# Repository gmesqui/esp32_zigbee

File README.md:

# ESP32-C5 / ESP32-C6 Zigbee Coordinator

Coordinador Zigbee completo para `ESP32-C5-KITC-A V1.2` y `ESP32-C6 Super Mini` con `ESP-IDF` y `ESP Zigbee SDK`.

Todo dispositivo con microcontrolador del proyecto debe admitir actualizaciones por su red de comunicaciones. La conexión física al ordenador queda como último recurso. El estado de los firmwares existentes y los criterios de aceptación se recogen en el [plan de actualización por red](PLAN.md).

## Hardware soportado

| Placa | Target ESP-IDF | Radio | Flash | LED RGB | Boton permit-join |
|-------|----------------|-------|-------|---------|-------------------|
| `ESP32-C5-KITC-A V1.2` | `esp32c5` | IEEE 802.15.4 nativa 2.4 GHz | 4 MiB | WS2812 GPIO 27 | GPIO 28 |
| `ESP32-C6 Super Mini` | `esp32c6` | IEEE 802.15.4 nativa 2.4 GHz | 4 MiB | WS2812 GPIO 8 | GPIO 9 |

- Ethernet: W5500 por SPI (`SPI2_HOST`)
- Consola: UART0 115200 baud en C5; USB Serial/JTAG nativo por USB-C en C6 Super Mini.
- La seleccion de pines se hace en `main/board_config.h` usando `CONFIG_IDF_TARGET`.

---

## Transporte WebSocket

El transporte operativo para clientes externos es WebSocket sobre ESP-IDF:

- Nombre mDNS del coordinador: `esp32-zigbee.local`
- Panel web: `http://esp32-zigbee.local:8080/`
- URL: `ws://esp32-zigbee.local:8080/ws`
- Modulo servidor: `ws_transport.c/h`
- Protocolo y parsing: `ws_protocol.c/h`
- Adaptacion del modelo interno: `ws_model.c/h`
- Sesion activa: `ws_client_session.c/h`
- Puente de productores Zigbee/modelo: `client_events.c/h`
- Self-test por UART: tecla `w`

Al conectarse un cliente, el ESP32 inicia el stream autonomo sin esperar un
mensaje entrante: envia `hello_ack`, inventario fragmentado, estado inicial y
despues queda en modo stream para eventos futuros.

---

## Arquitectura

```
app_main()
  ├─ nvs_flash_init()
  ├─ dm_init()              ← tabla RAM de dispositivos
  ├─ nvs_cache_load()       ← restaura registros desde NVS
  ├─ zcl_handler_init()     ← cache de atributos
  ├─ di_init()              ← maquina de estados de entrevista
  ├─ led_driver_init()      ← tarea LED @ 50 Hz
  ├─ button_handler_init()  ← ISR boton BOOT
  ├─ serial_cmd_init()      ← tarea UART0
  └─ zigbee_core_init()     ← tarea Zigbee + main loop (nunca retorna)
```

### Tareas FreeRTOS

| Tarea | Prioridad | Proposito |
|-------|-----------|-----------|
| `zigbee_main` | 5 | Loop principal del stack Zigbee |
| `btn_task` | 3 | Procesador de eventos de boton |
| `led_task` | 2 | Animacion LED @ 50 Hz |
| `serial_cmd_task` | 1 | Listener consola activa (`UART0` en C5, `USB Serial/JTAG` en C6) |

### Ficheros fuente

| Fichero | Responsabilidad |
|---------|----------------|
| `main.c` | Punto de entrada, secuencia de inicializacion |
| `board_config.h` | Seleccion de placa, pines de LED/boton/Ethernet y nombre de hardware por target ESP-IDF |
| `zigbee_core.c/h` | Init coordinador, manejador de senales BDB/ZDO, manejador de acciones ZCL, alarmas de mantenimiento |
| `device_manager.c/h` | Tabla RAM thread-safe (max 32 dispositivos), ciclo de vida, lookups por IEEE/NWK |
| `device_interview.c/h` | Maquina de estados de entrevista (7 pasos), cola FIFO, callbacks ZDO, resolucion IEEE |
| `zcl_handler.c/h` | Decodificacion de Report Attributes y Read Attribute Responses, cache con deteccion de cambios |
| `report_config.c/h` | Envio de Configure Reporting tras entrevista (13 clusters), respuesta IAS enrollment |
| `nvs_cache.c/h` | Serializacion/deserializacion binaria de dispositivos en NVS, escrituras lazy por bandera dirty |
| `serial_cmd.c/h` | Comandos interactivos por consola activa (teclas 1–5, g, w, n, j, r, e, ?) |
| `led_driver.c/h` | Control WS2812: onda seno verde-azul base, overlay rojo permit-join, overlay blanco actividad |
| `button_handler.c/h` | ISR con antirebote 200 ms, toggle permit-join 180 s |
| `utils.c/h` | Uptime ms/s, IEEE→string, nombres de cluster/device-type, macro `ZB_LOG` con timestamp |

---

## Funcionalidades implementadas

### Coordinador Zigbee

- Perfil Home Automation (0x0104), dispositivo Home Gateway (0x0050)
- Radio nativa, sin modo host
- Max 20 hijos (routers + end devices)
- Endpoint 1 con clusters Basic e Identify
- Mascara de canales: todos los canales 2.4 GHz
- Persistencia de red en NVS (namespace Zigbee stack): canal, PAN ID, ext PAN ID, clave de red

### Tabla de dispositivos en RAM

- 32 slots, protegida con mutex
- Estado por dispositivo: `NEW` → `INTERVIEWING` → `INTERVIEWED` → `CONFIGURED` → `FAILED`
- Campos por dispositivo:
  - `ieee`, `nwk_addr`, `friendly_name`
  - `online`, `is_sleepy`
  - `manufacturer`, `model`, `power_source`
  - `node_desc_flags`, `mac_capability_flags`, `manufacturer_code`, `power_desc_flags`
  - Hasta 8 endpoints, cada uno con `profile_id`, `device_id`, `clusters_in[]`, `clusters_out[]`
  - `last_seen_ms`, `lqi`, `rssi`
  - `reporting_configured`
  - Lecturas: `temperature_c`, `humidity_pct`, `on_off`, `occupancy`, `illuminance_raw`, `illuminance_lux`, `pressure_kpa`, `ias_zone_status`, `battery_mv`, `battery_pct`, `level`, `power_watts`
  - Contadores: `report_attr_ok`, `report_attr_unchanged`, `read_rsp_ok`, `read_rsp_fail`, `interview_attempts`

### Entrevista automatica (7 pasos)

1. Node Descriptor Request (ZDO)
2. Power Descriptor Request (ZDO)
3. Active Endpoints Request (ZDO)
4. Simple Descriptor Request por endpoint (ZDO)
5. Read Basic Cluster (0x0000, attrs: fabricante, modelo, fuente de alimentacion)
6. Read Power Config (0x0001, attrs: tension y porcentaje de bateria)
7. Configure Reporting (13 clusters estandar)

- Reintentos: 3 con backoff; marca FAILED si se agotan
- Cola FIFO de 8 posiciones para joins simultaneos
- Resolucion asıncrona de IEEE Address si se desconoce la direccion corta

### Clusters soportados para reporte / lectura

| Cluster | Nombre | Atributos relevantes |
|---------|--------|----------------------|
| 0x0001 | POWER_CFG | Tension bateria (0x0020), porcentaje (0x0021) |
| 0x0006 | ON_OFF | Estado encendido (0x0000) |
| 0x0008 | LEVEL | Nivel (0x0000, 0–254) |
| 0x0300 | COLOR_CTRL | Hue, Saturation, Color Temperature |
| 0x0400 | ILLUMINANCE | Iluminancia raw + conversion log a lux |
| 0x0402 | TEMPERATURE | Temperatura int16 ÷ 100 → °C |
| 0x0403 | PRESSURE | Presion int16 ÷ 10 → kPa |
| 0x0405 | HUMIDITY | Humedad uint16 ÷ 100 → % |
| 0x0406 | OCCUPANCY | Bitmap presencia |
| 0x0500 | IAS_ZONE | Estado zona alarma + enrollment |
| 0x0B04 | ELEC_MEAS | Potencia activa (0x050B) |

### Configure Reporting enviado tras entrevista

| Cluster | Atributo | Tipo | Min (s) | Max (s) | Threshold |
|---------|----------|------|---------|---------|-----------|
| 0x0006 | 0x0000 | bool | 0 | 3600 | — |
| 0x0008 | 0x0000 | uint8 | 1 | 3600 | 1 |
| 0x0300 | 0x0000, 0x0001 | uint8 | 1 | 3600 | 1 |
| 0x0300 | 0x0007 | uint16 | 1 | 3600 | 10 |
| 0x0402 | 0x0000 | int16 | 10 | 3600 | 10 |
| 0x0405 | 0x0000 | uint16 | 10 | 3600 | 50 |
| 0x0403 | 0x0000 | int16 | 10 | 3600 | 10 |
| 0x0400 | 0x0000 | uint16 | 10 | 3600 | 500 |
| 0x0406 | 0x0000 | bitmap8 | 0 | 3600 | — |
| 0x0001 | 0x0021 | uint8 | 3600 | 43200 | 2 |
| 0x0500 | 0x0002 | bitmap16 | 0 | 3600 | — |
| 0x0B04 | 0x050B | int16 | 5 | 3600 | 10 |

### Deteccion de presencia (offline)

- **Siempre encendido**: lectura de confirmacion al llegar a `max_interval + presence_probe_grace_s`; offline al llegar a `max_interval + presence_offline_grace_s` si no hubo respuesta.
- **Sleepy (bateria)**: sin sondeo activo; offline al llegar a `max_interval + presence_offline_grace_s`.
- Verificacion cada 10 s via alarma de mantenimiento
- Para dispositivos siempre encendidos, `presence_probe_grace_s` es el margen bajo que dispara una lectura ZCL de confirmacion; `presence_offline_grace_s` es el margen alto que certifica offline si no hubo respuesta ni otro trafico.

### Persistencia NVS de dispositivos

- Namespace: `zb_cache`
- Claves: `dt3_head` (version + count), `dt3_d00`–`dt3_d31` (blobs por dispositivo)
- Version de esquema: **3** (los blobs de versiones anteriores se rechazan)
- Escritura lazy: solo los registros con bandera `dirty` se escriben; se limpia tras commit
- Periodicidad: cada 10 s via alarma de mantenimiento (solo si hay cambios)
- Al arrancar: los dispositivos restaurados vuelven con estado INTERVIEWED, `online=false`
- `last_seen` y cambios de RSSI/LQI NO disparan escritura NVS

> Si ves `ESP_ERR_NVS_NOT_ENOUGH_SPACE` al guardar `dt3_d31`, no reduzcas la particion `nvs` (actualmente 128 KiB).

### LED WS2812

| Estado | Patron |
|--------|--------|
| Normal | Onda seno verde-azul, periodo 4 s |
| Permit-join abierto | Overlay rojo pulsante, periodo 1 s |
| Actividad ZCL | Flash blanco 100 ms con decay |

### Boton BOOT

- Pulsacion corta: abre permit-join 180 s (o cierra si ya estaba abierto)
- Antirebote hardware: 200 ms

### Patillaje Ethernet (W5500 por SPI)

| Senal | ESP32-C5 GPIO | ESP32-C6 GPIO | Notas |
|-------|---------------|---------------|-------|
| `MOSI` | 4 | 2 | SPI hacia el W5500 |
| `MISO` | 5 | 3 | SPI desde el W5500 |
| `SCLK` | 6 | 6 | Reloj SPI |
| `CS` | 23 | 7 | Chip select del W5500 |
| `INT` | 24 | 18 | Interrupcion del W5500 |
| `RST` | 25 | 14 | Reset del W5500 |

- Host SPI usado: `SPI2_HOST`
- Frecuencia SPI configurada: `20 MHz`

---

## Comandos serie

Canal interactivo segun target:

- `ESP32-C5`: `UART0` a `115200`
- `ESP32-C6`: `USB Serial/JTAG` nativo por USB-C

| Tecla | Accion |
|-------|--------|
| `1` | Emite JSON completo con tabla de dispositivos |
| `2` | Estadisticas de red (canal, PAN ID, ext PAN ID, IEEE coordinador, conteo online) |
| `3` | Lista de tareas FreeRTOS (nombre, estado, prioridad, stack) |
| `4` | Estadisticas de heap (libre actual, minimo historico) |
| `5` | Estado de la cola de entrevista |
| `n` | Asignar nombre amigable a un dispositivo (pide IEEE y nombre) |
| `j` | Toggle permit-join (abre 180 s o cierra) |
| `r` | Re-entrevistar dispositivo (pide IEEE, resetea estado a NEW) |
| `e` | Borrar cache NVS (pide confirmacion "YES") |
| `w` | Ejecutar self-test del protocolo WebSocket |
| `?` | Ayuda: imprime mapa de teclas |

---

## Formato de log

Cuando el reloj SNTP ya es valido, los logs usan fecha y hora local segun la
zona horaria configurada. Mientras el reloj no sea valido, usan timestamp
relativo al arranque:

```
[2026-04-26 20:35:12.123]
[T+%07.3f]  ->  [T+012.345]
```

Por cada mensaje ZCL/ZDO se emiten hasta 3 lineas:

1. `RAW` — bytes en hexadecimal y metadatos APS/NWK
2. `DECODE` — campos interpretados (profile, cluster, seq, etc.)
3. `IMPACT` — significado del mensaje y evento local desencadenado

---

## Salida JSON (tecla `1`)

```json
{
  "ts_s": 123.456,
  "device_count": 2,
  "devices": [
    {
      "ieee": "0x00124B00AABBCCDD",
      "friendly_name": "Sensor salon",
      "short": "0x1234",
      "online": true,
      "is_sleepy": false,
      "manufacturer": "Sonoff",
      "model": "SNZB-02",
      "power_source": "battery",
      "state": "configured",
      "last_seen_s": 120.123,
      "lqi": 189,
      "rssi": -56,
      "reporting_configured": true,
      "endpoints": [
        {
          "id": 1,
          "profile": "0x0104",
          "device_id": "TEMP_SENSOR",
          "in_clusters": ["0x0000", "0x0001", "0x0003", "0x0402", "0x0405"],
          "out_clusters": ["0x0019"]
        }
      ],
      "readings": {
        "temperature_c": 21.45,
        "humidity_pct": 58.12,
        "battery_mv": 3000,
        "battery_pct": 85
      },
      "stats": {
        "report_attr_ok": 42,
        "report_attr_unchanged": 18,
        "read_rsp_ok": 7,
        "read_rsp_fail": 1,
        "interview_attempts": 1
      }
    }
  ]
}
```

Solo se incluyen en `readings` las claves que tienen dato (no se emiten `null`).
Si la iluminancia raw es 0 (demasiado baja), no se incluye `illuminance_lux`.

Comportamiento ante informes repetidos: `last_seen_s` se actualiza siempre; `report_attr_ok` y los logs de valor solo se emiten si el dato **cambia** respecto al almacenado; `report_attr_unchanged` cuenta los que no alteraron el dato.

---

## Limites y constantes clave

| Constante | Valor | Notas |
|-----------|-------|-------|
| `MAX_DEVICES` | 32 | Slots en tabla RAM |
| `MAX_ENDPOINTS` | 8 | Por dispositivo |
| `MAX_CLUSTERS_PER_EP` | 32 | Entrada + salida combinados |
| `FRIENDLY_NAME_LEN` | 33 | 32 chars + NUL |
| `MAX_ATTR_CACHE` | 128 | Entradas cache de atributos |
| `MAX_PENDING_ATTRS` | 8 | Buffer para direcciones desconocidas |
| `IQUEUE_SIZE` | 8 | Cola FIFO de entrevista |
| `MAX_CHILDREN` | 20 | Routers + end devices |
| `MAINTENANCE_PERIOD_MS` | 10 000 | NVS flush + deteccion presencia |
| `OFFLINE_THRESHOLD_ALWAYS_ON_MS` | 7 260 000 | ~2 h |
| `OFFLINE_THRESHOLD_SLEEPY_MS` | 10 920 000 | ~3 h |
| `PERMIT_JOIN_SECS` | 180 | Ventana abierta por boton |
| `DEBOUNCE_MS` | 200 | Antirebote boton |
| `LED_STRIP_GPIO` | C5: 27, C6: 8 | GPIO WS2812 |
| `BOOT_BUTTON_GPIO` | C5: 28, C6: 9 | GPIO boton BOOT |
| `ETH_MOSI_GPIO` | C5: 4, C6: 2 | SPI MOSI hacia W5500 |
| `ETH_MISO_GPIO` | C5: 5, C6: 3 | SPI MISO desde W5500 |
| `ETH_SCLK_GPIO` | C5: 6, C6: 6 | SPI clock W5500 |
| `ETH_CS_GPIO` | C5: 23, C6: 7 | Chip select W5500 |
| `ETH_INT_GPIO` | C5: 24, C6: 18 | Interrupcion W5500 |
| `ETH_RST_GPIO` | C5: 25, C6: 14 | Reset W5500 |
| `ETH_SPI_CLOCK_HZ` | 20 000 000 | SPI Ethernet a 20 MHz |
| `NVS_CACHE_VERSION` | 3 | Version de esquema NVS |

---

## Particiones

```
nvs,        data, nvs,     0x9000,   0x20000    # 128 KiB — NVS (cache + stack Zigbee)
phy_init,   data, phy,     0x29000,  0x1000     #   4 KiB — calibracion PHY
zb_storage, data, fat,     0x2A000,  0x10000    #  64 KiB — almacenamiento persistente Zigbee
zb_fct,     data, fat,     0x3A000,  0x1000     #   4 KiB — factory data Zigbee
otadata,    data, ota,     0x3C000,  0x2000
ota_0,      app,  ota_0,   0x40000,  0x1E0000
ota_1,      app,  ota_1,   0x220000, 0x1E0000
```

> Si cambias los offsets de `zb_storage` / `zb_fct`, hay que flashear la tabla de particiones y puede ser necesario volver a formar la red.

---

## Activar entorno ESP-IDF

Para macOS, consulta [Entorno de desarrollo en macOS](docs/entorno-macos.md),
con las herramientas instaladas, la activación del entorno y los comandos para
compilar ambas placas y ejecutar las aplicaciones del proyecto.

En PowerShell:

```powershell
. "C:\Espressif\tools\Microsoft.v5.5.3.PowerShell_profile.ps1"
```

## Compilar

Para ESP32-C5:

```powershell
idf.py set-target esp32c5
idf.py build
```

Para ESP32-C6:

```powershell
idf.py set-target esp32c6
idf.py build
```

`sdkconfig.defaults` contiene la configuracion comun, y `sdkconfig.defaults.esp32c5` / `sdkconfig.defaults.esp32c6` contienen los ajustes especificos de cada target.

## Actualizar por Ethernet

El coordinador C5 y el C6 admiten imágenes de aplicación firmadas sobre Ethernet. Para la migración de una unidad ya emparejada, la actualización ordinaria y la comprobación de dispositivos, sigue la [guía OTA](docs/ota-ethernet.md).

## Flashear y monitorizar

```powershell
.\flash-monitor.ps1
```

Solo monitorizar:

```powershell
.\monitor.ps1
```

Flashear con argumentos adicionales:

```powershell
.\idf-with-com7.ps1 flash monitor
```

En ESP32-C6 Super Mini, usa el puerto COM del USB-C nativo de la placa; `sdkconfig.defaults.esp32c6` deja la consola en USB Serial/JTAG.

Salir del monitor: `Ctrl+]`

---

## Plugin Homebridge

El plugin de Homebridge vive en una carpeta separada del firmware:

- [homebridge-plugin/README.md](/c:/projects/esp32_zigbee3/homebridge-plugin/README.md)

Se apoya en el protocolo WebSocket documentado en:

- [docs/protocolo_websocket_esp32_homebridge_v2.docx](/c:/projects/esp32_zigbee3/docs/protocolo_websocket_esp32_homebridge_v2.docx)

Objetivo del paquete:

- conectar Homebridge como cliente WebSocket al ESP32
- descubrir accesorios desde `inventory_chunk`
- mantener estado y reachability desde `state_chunk` y `event`
- traducir comandos HomeKit hacia `cmd`

El plugin se ha separado a nivel de repo para no mezclar dependencias Node/Homebridge
con el firmware ESP-IDF.

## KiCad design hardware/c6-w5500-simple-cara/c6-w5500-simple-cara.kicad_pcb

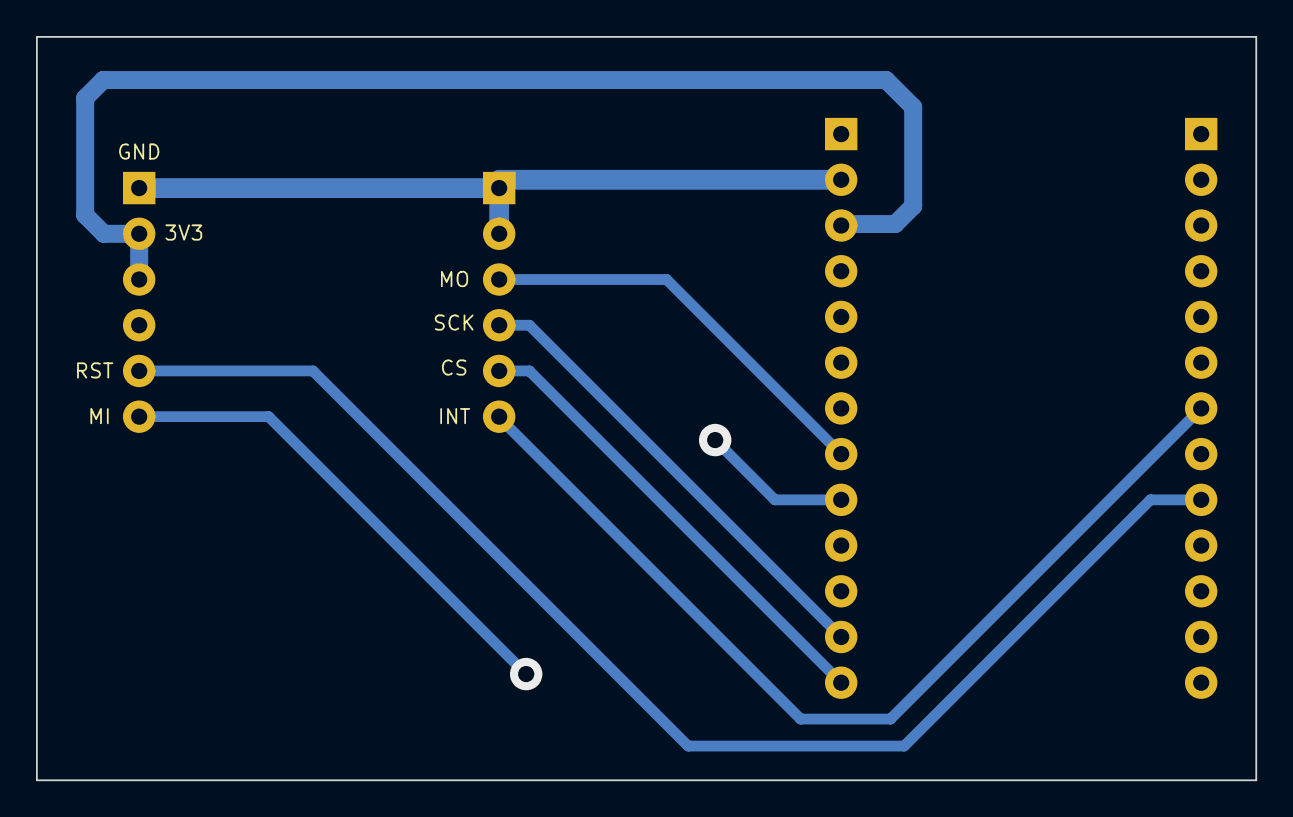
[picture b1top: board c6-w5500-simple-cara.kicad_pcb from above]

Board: 2 copper layers, 67.7 x 41.3 mm, 4 parts (0 on the bottom side), 8 nets.

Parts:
J1: W5500_LEFT; PinHeader_1x06_P2.54mm_Vertical
J2: W5500_RIGHT; PinHeader_1x06_P2.54mm_Vertical
J3: C6_LEFT; PinHeader_1x13_P2.54mm_Vertical
J4: C6_RIGHT; PinHeader_1x13_P2.54mm_Vertical

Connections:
+3V3: J1.2 (V), J1.3 (V), J3.3 (3V3)
CS_GPIO7: J2.5 (CS), J3.13 (GPIO7)
GND: J1.1 (G), J2.1 (G), J2.2 (G), J3.2 (GND)
INT_GPIO18: J2.6 (INT), J4.7 (GPIO18)
MISO_GPIO3: J1.6 (MI), J3.9 (GPIO3)
MOSI_GPIO2: J2.3 (MO), J3.8 (GPIO2)
RST_GPIO14: J1.5 (RST), J4.9 (GPIO14)
SCLK_GPIO6: J2.4 (SCK), J3.12 (GPIO6)
